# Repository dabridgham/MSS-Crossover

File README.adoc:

= MSS Crossover

A KiCad project for a circuit board that implements an
https://www.modularsignalsystem.info/index.html[MSS] Crossover node.
It includes the block detection circuit and the crossover wiring
between two RJ45 connectors.

See the https://github.com/dabridgham/MSS-Crossover/wiki[wiki] for more information.

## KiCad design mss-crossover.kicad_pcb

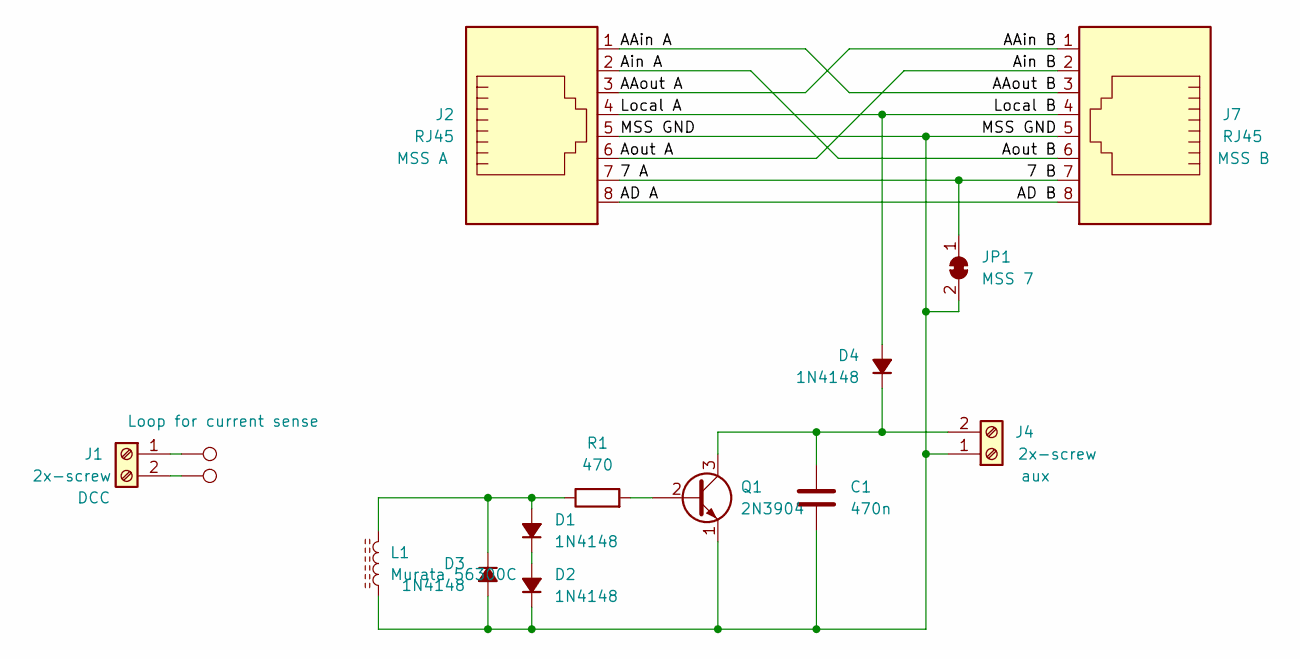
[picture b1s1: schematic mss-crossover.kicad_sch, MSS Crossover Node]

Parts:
C1: 470n; C_Disc_D7.5mm_W2.5mm_P5.00mm; MPN FG28X7R1H474KRT06
D1, D2, D3, D4: 1N4148; D_DO-35_SOD27_P7.62mm_Horizontal; MPN 1N4148FS-ND
J1, J4: 2x-screw; CUI_TB003-500-P02BE; MPN TB003-500-P02BE
J2, J7: RJ45; MJ3221-88; MPN MJ3221-88
JP1: MSS 7; SolderJumper-2_P1.3mm_Bridged_RoundedPad1.0x1.5mm
L1: Murata 56300C; Murata_56300C; MPN 56300C
Q1: 2N3904; TO-92_Inline_Wide; MPN 2N3904TA
R1: 470; R_Axial_DIN0207_L6.3mm_D2.5mm_P10.16mm_Horizontal; MPN CF14JT470R
TP1: Loop for current sense; TestPoint_THTPad_D2.0mm_Drill1.0mm
TP2: TestPoint_THTPad_D2.0mm_Drill1.0mm

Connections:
/7 A: J2.7, J7.7, JP1.1 (A)
/AAin A: J2.1, J7.3
/AAin B: J2.3, J7.1
/AD A: J2.8, J7.8
/Ain A: J2.2, J7.6
/Ain B: J2.6, J7.2
/Local A: D4.2 (A), J2.4, J7.4
/MSS GND: C1.2, D2.1 (K), D3.2 (A), J2.5, J4.1, J7.5, JP1.2 (B), L1.2, Q1.1 (E)
unnamed: D1.2 (A), D3.1 (K), L1.1, R1.1
unnamed: D1.1 (K), D2.2 (A)
unnamed: C1.1, D4.1 (K), J4.2, Q1.3 (C)
unnamed: J1.1, TP1.1
unnamed: J1.2, TP2.1
unnamed: Q1.2 (B), R1.2

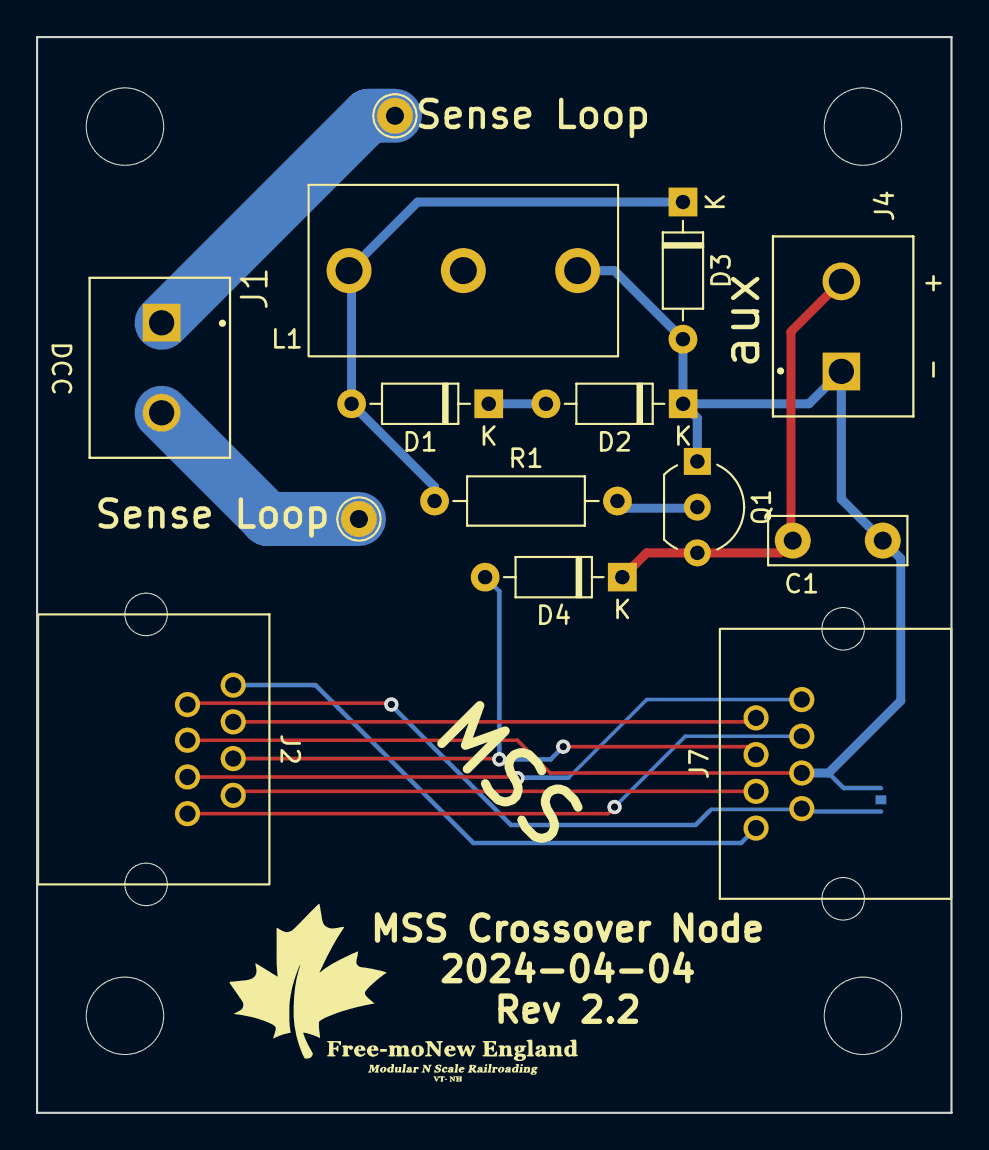
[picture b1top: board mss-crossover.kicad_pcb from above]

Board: 2 copper layers, 50.8 x 59.8 mm, 15 parts (1 on the bottom side), 14 nets.

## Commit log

2024-02-25 Changed RJ45s to have their tab up instead of down. Have already done a first run of these boards called v0.2. Updated the version here to be 2.1
2024-03-09 Changed MPN for the RJ45 to RJHSE-5080
2024-03-09 Added README
2024-03-09 Added notes about how to use the AUX terminal
2024-03-09 Added note about the 'sense loop' wire.
2024-03-09 Update README.adoc
    Made the Notes section into a list.
2024-03-12 Update README.adoc
    Moved the Notes to the wiki
2024-03-12 Added the BoM as both csv and html
2024-03-12 removed header that was confusing GitHub
2024-03-12 Still need the csv header though
2024-03-12 Moving that pre-amble to the end to see if that works
2024-03-12 Nope, GitHub didn't like that. So no meta-data in the csv file
2024-03-12 Not going to bother with the HTML BoM since GitHub can't display it nicely.
2024-07-02 Changed connectors to MJ3221-88 (the yellow ones that Ryan found) and put the connectors on opposite edges of the board (like everyone but me likes). Also updated the footprint for the pulse transfor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
2024-07-02 updated BoM for v2.2 board
2024-07-02 Added MPN to BoM
